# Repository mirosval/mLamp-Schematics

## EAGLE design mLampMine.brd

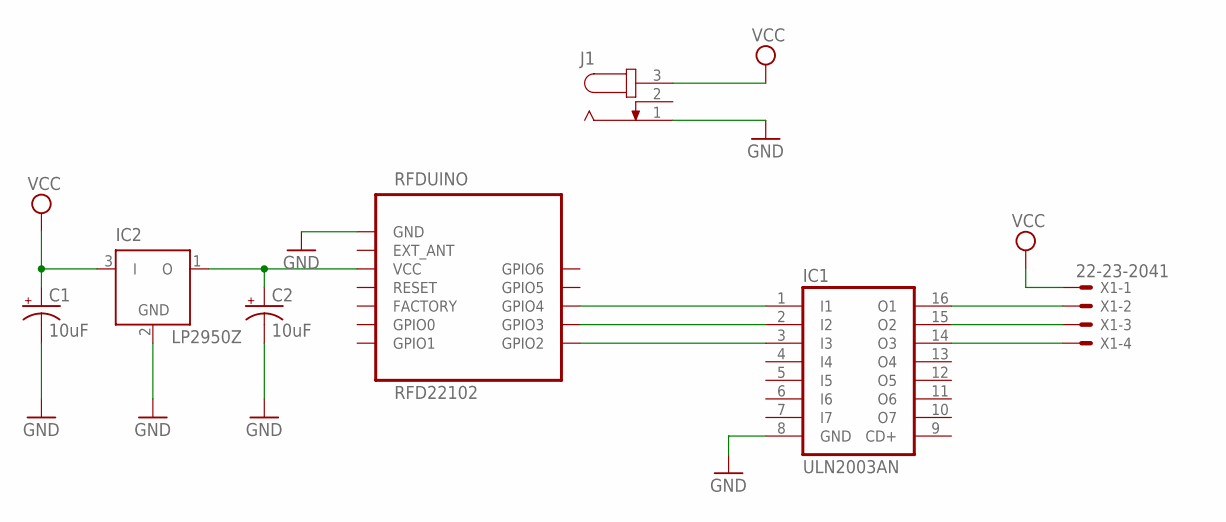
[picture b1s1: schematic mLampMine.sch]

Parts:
C1, C2: 10uF; CPOL-RADIAL-10UF-25V
IC1: ULN2003AN; DIL16
IC2: LP2950Z; TO92
J1: JACK-PLUG0; SPC4077
RFDUINO: RFD22102
X1: 22-23-2041

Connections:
GND: C1.2 (-), C2.2 (-), IC1.8 (GND), IC2.2 (GND), J1.1, RFDUINO.GND
unnamed: IC1.2 (I2), RFDUINO.GPIO3
unnamed: IC1.1 (I1), RFDUINO.GPIO4
unnamed: IC1.3 (I3), RFDUINO.GPIO2
unnamed: C2.1 (+), IC2.1 (O), RFDUINO.VCC
unnamed: IC1.14 (O3), X1.4
unnamed: IC1.15 (O2), X1.3
unnamed: IC1.16 (O1), X1.2
VCC: C1.1 (+), IC2.3 (I), J1.3, X1.1

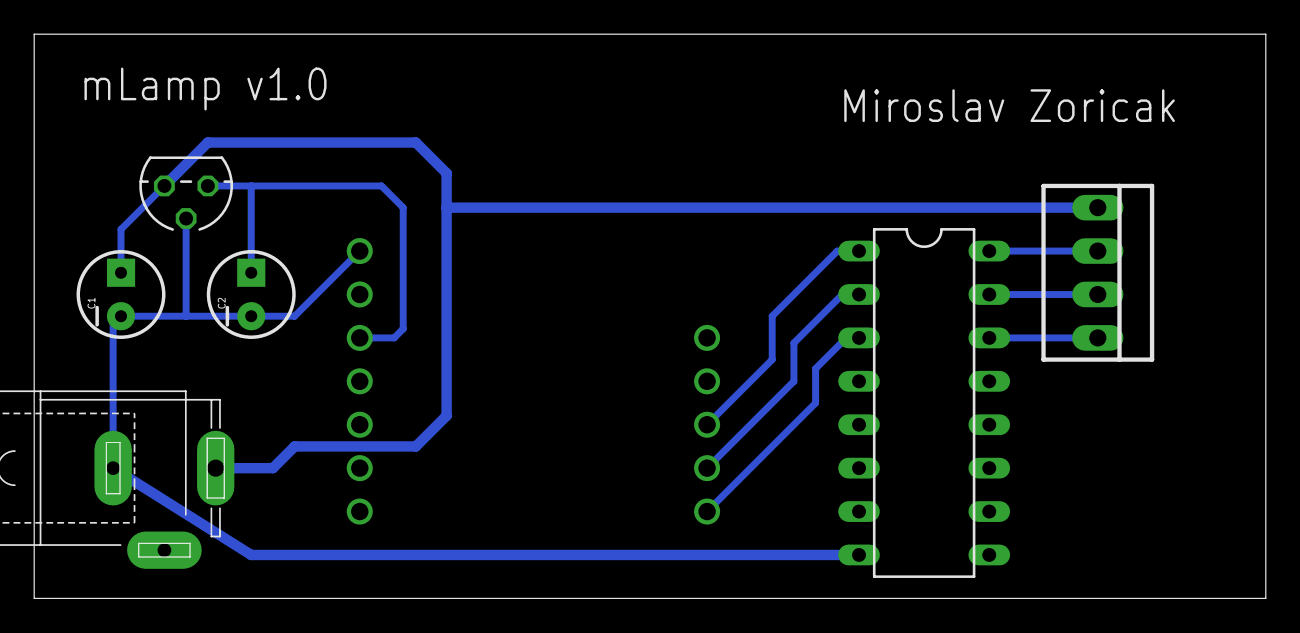
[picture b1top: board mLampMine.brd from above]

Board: 2 copper layers, 72.1 x 33.0 mm, 7 parts (0 on the bottom side), 9 nets.

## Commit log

2015-09-27 Create LICENSE

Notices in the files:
parts and their libraries:
SparkFun-Capacitors: Licensing: Creative Commons ShareAlike 4.0 International - https://creativecommons.org/licenses/by-sa/4.0
